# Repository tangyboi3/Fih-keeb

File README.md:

# Fih keeb
Fih keeb. 23332+2, very staggered, made using ergogen.

## BOM
| Name | Qt | Notes|
| :--- | :---: | :--- |
| Fih pcbs | 2 | gerbers [here](./pcb/gerbers) |
| nice!nanos or clones | 2 | i used [these](https://www.aliexpress.us/item/3256806824240477.html) |
| female headers | 48 | make sure you get the shortest ones, ph3.5. [ali](https://www.aliexpress.us/item/3256806227209544.html) |
| 301230 LiPos | 2 | any size that can fit under the n!n will work, i used [these](https://www.aliexpress.us/item/3256809270469725.html) |
| JST PH 2.0 connectors | 2 | [ali](https://www.aliexpress.us/item/3256804769340392.html) |
| choc v1 or v2 switches and keycaps | 30 | duh |
| SS12D00 power switches | 2 | [ali](https://www.aliexpress.us/item/3256810241242670.html) |
| TS-1136 reset buttons | 2 | make sure you get the DIP version. [ali](https://www.aliexpress.us/item/3256801442870232.html) |
| rubber feet | 8 | [ali](https://www.aliexpress.us/item/3256805129083590.html) |
> note: solder the n!n component side down. solder the jumpers on the back of the pcb relative to the keys. the n!n footprint silkscreen has a reminder.

## firmware
[here](https://github.com/tangyboi3/zmk-keyboard-fih/)

## thanks
thanks to mrzealot for [ergogen](https://ergogen.ceoloide.com/), ceoloide for their fork and [footprints](https://github.com/ceoloide/ergogen-footprints/), genteure for the neat [zmk shield wizard](https://shield-wizard.genteure.com/), [zmk](https://v0-3-branch.zmk.dev/) itself for the firmware, the [hummingbird](https://github.com/PJE66/hummingbird), [berylline](https://github.com/jcmkk3/trochilidae#berylline), [pueo](https://github.com/grassfedreeve/pueo/), [i'iwi](https://github.com/grassfedreeve/iiwi), and [fitis](https://github.com/weteor/Fitis) keyboards for inspiration, and @car_kaboomer on discord for all the help.

## todo
get pictures from a respectable camera

maybe make a case

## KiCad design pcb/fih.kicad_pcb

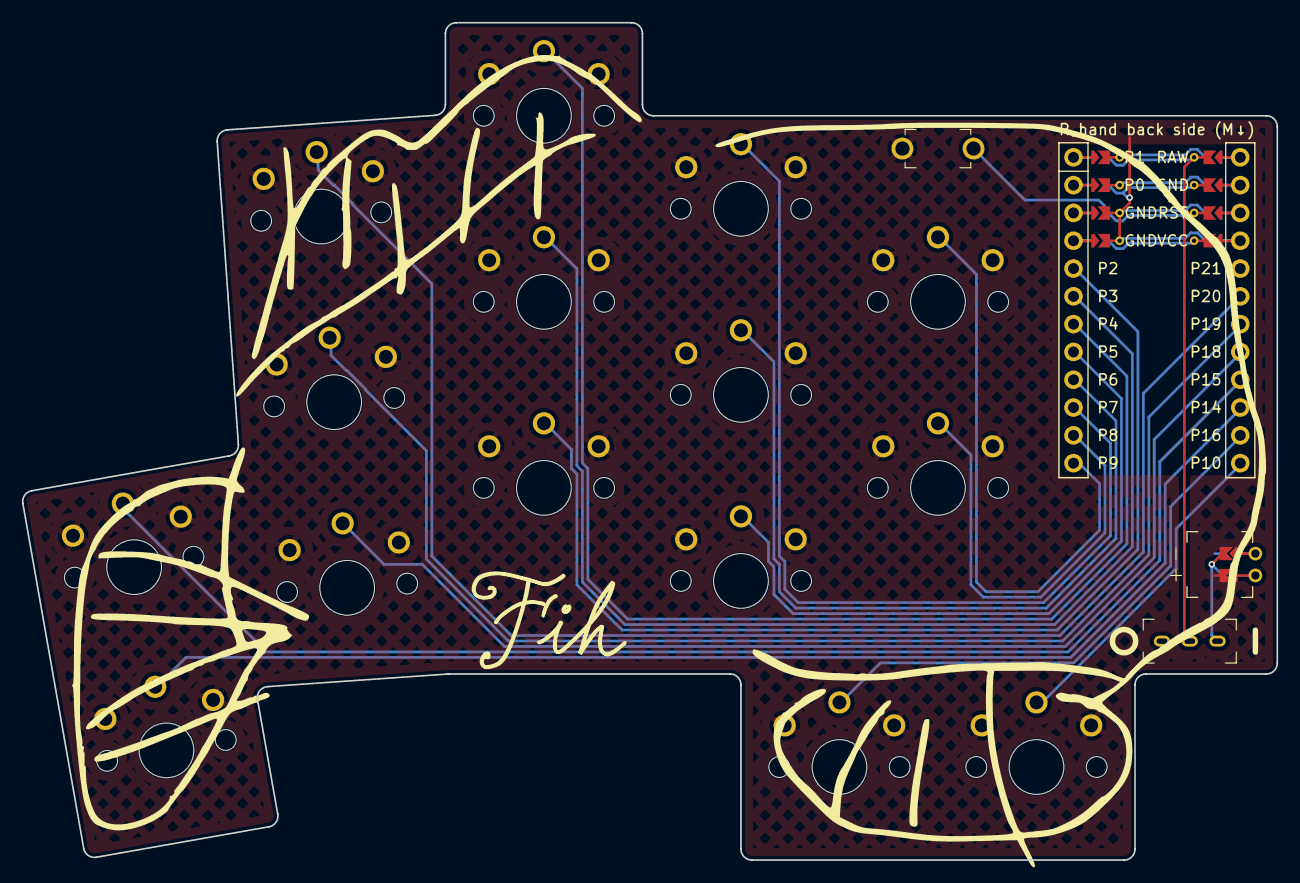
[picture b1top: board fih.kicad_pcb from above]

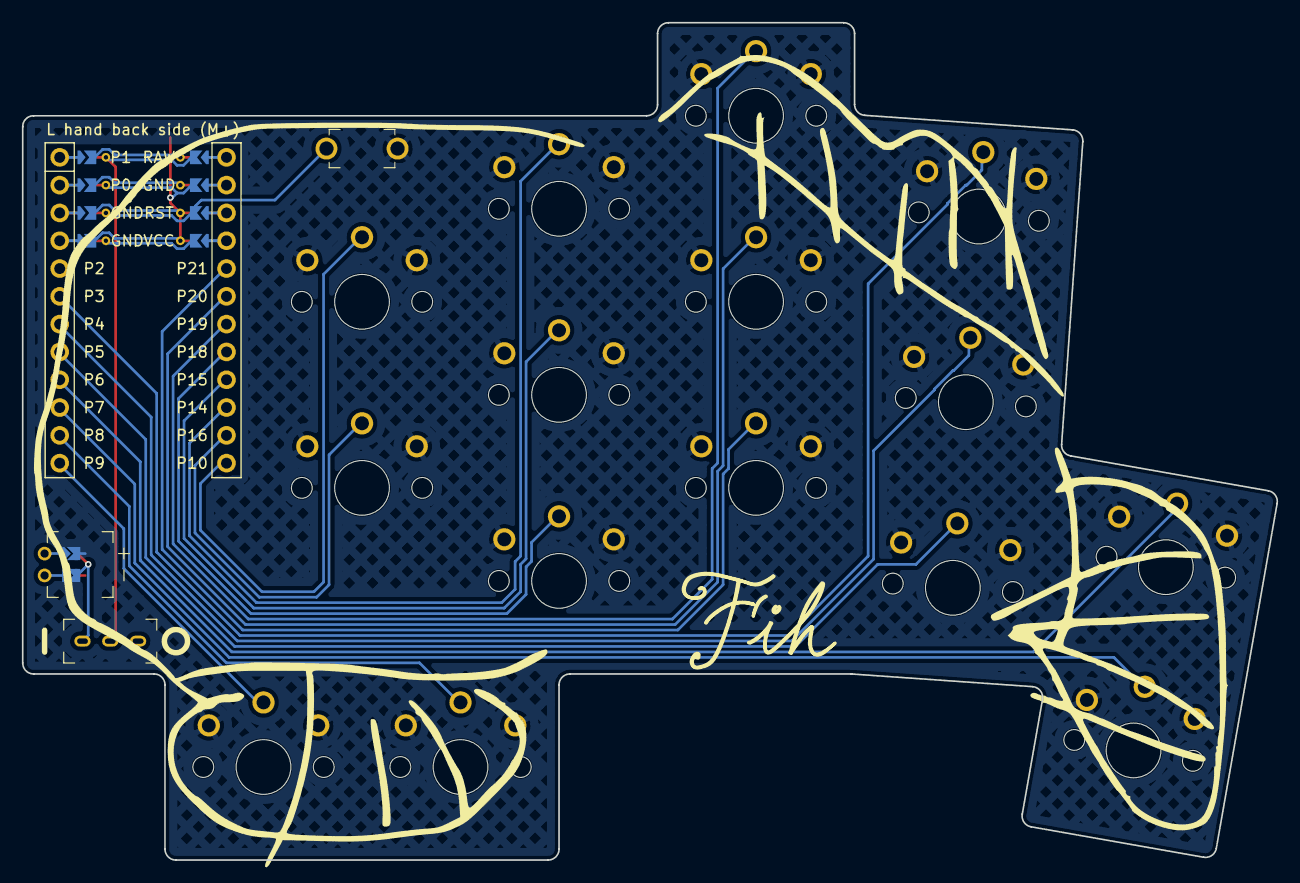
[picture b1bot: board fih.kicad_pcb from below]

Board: 2 copper layers, 114.6 x 76.5 mm, 19 parts (14 on the bottom side), 21 nets.

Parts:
MCU1: mcu_supermini_nrf52840
PWR1: SS12D00
RST1: TS1236
S1, S2, S3, S4, S5, S6, S7, S8, S9, S10, S11, S12, S13, S14, S15: switch_choc_v1_v2
XX1: JSTPH2

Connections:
BAT_P: PWR1.BAT_P, XX1.BAT_P
GND: MCU1.102, MCU1.121, MCU1.122, RST1.GND, S1.1, S2.1, S3.1, S4.1, S5.1, S6.1, S7.1, S8.1, S9.1, S10.1, S11.1, S12.1, S13.1, S14.1, S15.1, XX1.BAT_N
JST1: XX1.1, XX1.21, XX1.31
JST2: XX1.2, XX1.22, XX1.32
RAW: MCU1.101, PWR1.RAW
RST: MCU1.103, RST1.RST
matrix_index_bottom: MCU1.17, S9.2
matrix_index_home: MCU1.16, S10.2
matrix_index_top: MCU1.15, S11.2
matrix_inner_home: MCU1.14, S12.2
matrix_inner_top: MCU1.13, S13.2
matrix_middle_bottom: MCU1.20, S6.2
matrix_middle_home: MCU1.19, S7.2
matrix_middle_top: MCU1.18, S8.2
matrix_pinky_bottom: MCU1.10, S1.2
matrix_pinky_home: MCU1.9, S2.2
matrix_ring_bottom: MCU1.8, S3.2
matrix_ring_home: MCU1.7, S4.2
matrix_ring_top: MCU1.6, S5.2
thumbs_reachy: MCU1.12, S15.2
thumbs_tucky: MCU1.11, S14.2
